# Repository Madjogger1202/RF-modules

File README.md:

# RF-modules

**Серия экспериментальных ВЧ-плат: широкополосные усилители и пассивные фильтры Чебышёва.**

Небольшая коллекция тестовых радиочастотных плат, собранная в процессе погружения в тему ВЧ-усилителей и согласования сигналов. Идея — спроектировать набор готовых строительных блоков (усилитель, транзисторный каскад, фильтры), чтобы в нужный момент сразу взять проверенный модуль с полки. Каждая плата оформлена как отдельный проект внутри репозитория.

## Состав репозитория

| Папка | Тип | Краткое описание |
|---|---|---|
| `BGA2869 amplifier` | Усилитель | MMIC-усилитель BGA2869, DC–2.2 ГГц, ~30 dB |
| `MMBF5485 amplifier` | Усилитель | Каскад на N-канальном ВЧ JFET MMBF5485 + обвязка |
| `Chebyshev_4_filter` | Фильтр | LC-фильтр Чебышёва 4-го порядка |
| `Chebyshev_10_filter` | Фильтр | LC-фильтр Чебышёва 10-го порядка |

---

## BGA2869 amplifier

Широкополосный усилитель на MMIC **BGA2869** (NXP) — недорогой и удобный «кирпичик» усиления с внутренним согласованием на 50 Ω, не требующий внешних согласующих цепей и выходного дросселя.

**Характеристики**

| Параметр | Значение |
|---|---|
| Активный элемент | BGA2869 (NXP MMIC, SOT363) |
| Полоса | DC … 2.2 ГГц |
| Усиление | ~31.7 dB @ 950 МГц |
| Коэффициент шума | 3.1 dB @ 950 МГц |
| Выходная мощность (P1dB) | ~10 dBm @ 950 МГц |
| Согласование | внутреннее, 50 Ω (вход/выход) |
| Питание | 5 В (~24 мА) |
| Вход питания | USB и DC-Jack |

Применение: универсальный широкополосный блок усиления, IF-усилитель, второй каскад после LNA. Сам чип стоит около 100 руб — плата получается очень бюджетной.

---

## MMBF5485 amplifier

Каскад на N-канальном ВЧ JFET **MMBF5485** (семейство 2N5484/5485/5486) с цепями смещения и согласования. Экспериментальная плата — основная цель проверить транзистор в роли ВЧ-усилителя. Если по усилению результат не устроит, обвязка спроектирована так, что плату можно переиспользовать как фильтр/согласующий модуль.

**Характеристики**

| Параметр | Значение |
|---|---|
| Активный элемент | MMBF5485 (N-канальный JFET, SOT-23) |
| Назначение | ВЧ-усилитель VHF/UHF диапазона |
| VGS(off) | −0.5 … −4 В |
| Крутизна (gfs) | от ~3.5 мС |
| Согласование | дискретная обвязка вход/выход |
| Резервное использование | фильтр / согласующий модуль |

---

## Фильтры Чебышёва (4 и 10 порядка)

Пассивные LC-фильтры с характеристикой Чебышёва: версии **4-го** (`Chebyshev_4_filter`) и **10-го** (`Chebyshev_10_filter`) порядков. Сделаны как готовые фильтрующие блоки на 50 Ω, чтобы держать под рукой для отладки и согласования трактов.

| Параметр | Chebyshev_4_filter | Chebyshev_10_filter |
|---|---|---|
| Тип | LC-фильтр Чебышёва | LC-фильтр Чебышёва |
| Порядок | 4 | 10 |
| Импеданс | 50 Ω | 50 Ω |
| Крутизна склона | пологая | крутая (больше секций) |

> 💡 Удобный онлайн-калькулятор LC-фильтров с подбором реальных номиналов компонентов:
> https://markimicrowave.com/technical-resources/tools/lc-filter-design-tool/

---

## Среда разработки

- **Схема и плата:** KiCad
- **Подбор фильтров:** Marki Microwave LC Filter Design Tool
- **Документация на компоненты:** datasheet BGA2869 (NXP), MMBF5485 (Fairchild/onsemi)

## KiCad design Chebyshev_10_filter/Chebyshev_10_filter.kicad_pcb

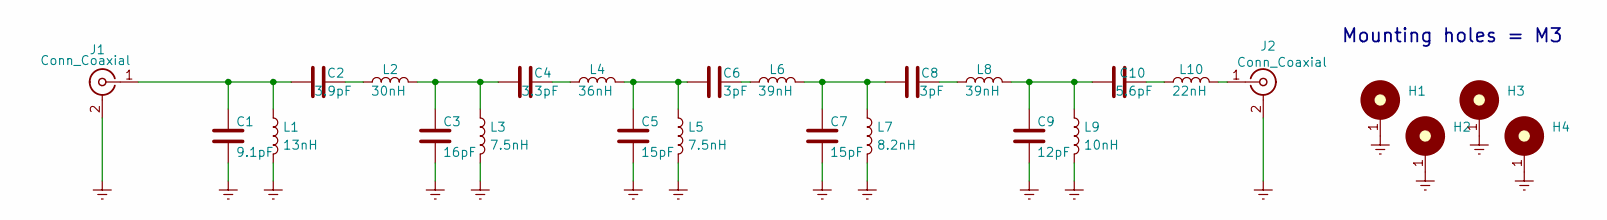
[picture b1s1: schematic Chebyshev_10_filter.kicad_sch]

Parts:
C1: 9.1pF; C_0402_1005Metric
C2: 3.9pF; C_0402_1005Metric
C3: 16pF; C_0402_1005Metric
C4: 3.3pF; C_0402_1005Metric
C5, C7: 15pF; C_0402_1005Metric
C6, C8: 3pF; C_0402_1005Metric
C9: 12pF; C_0402_1005Metric
C10: 5.6pF; C_0402_1005Metric
H1, H2, H3: MountingHole_M3_3.2mm_Pad; MountingHole_3.2mm_M3_DIN965_Pad_TopBottom
H4: MountingHole:MountingHole_3.2mm_M3_DIN965_Pad_Top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; MountingHole_3.2mm_M3_DIN965_Pad_TopBottom
J1, J2: Conn_Coaxial; SMA_Samtec_SMA-J-P-H-ST-EM1_EdgeMount
L1: 13nH; L_0402_1005Metric
L2: 30nH; L_0402_1005Metric
L3, L5: 7.5nH; L_0402_1005Metric
L4: 36nH; L_0402_1005Metric
L6, L8: 39nH; L_0402_1005Metric
L7: 8.2nH; L_0402_1005Metric
L9: 10nH; L_0402_1005Metric
L10: 22nH; L_0402_1005Metric

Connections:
Earth: C1.2, C3.2, C5.2, C7.2, C9.2, H1.1, H2.1, H3.1, H4.1, J1.2 (Ext), J2.2 (Ext), L1.2, L3.2, L5.2, L7.2, L9.2
unnamed: C2.2, L2.1
unnamed: C3.1, C4.1, L2.2, L3.1
unnamed: C4.2, L4.1
unnamed: C5.1, C6.1, L4.2, L5.1
unnamed: C6.2, L6.1
unnamed: C7.1, C8.1, L6.2, L7.1
unnamed: C8.2, L8.1
unnamed: C9.1, C10.1, L8.2, L9.1
unnamed: C10.2, L10.1
unnamed: C1.1, C2.1, J1.1 (In), L1.1
unnamed: J2.1 (In), L10.2

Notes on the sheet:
Mounting holes = M3

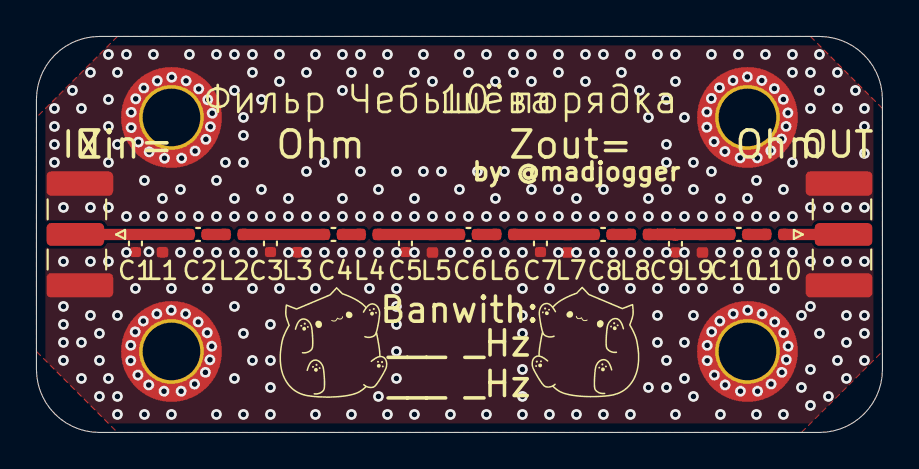
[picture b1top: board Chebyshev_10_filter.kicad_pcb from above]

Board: 2 copper layers, 47.0 x 22.0 mm, 26 parts (0 on the bottom side), 12 nets.

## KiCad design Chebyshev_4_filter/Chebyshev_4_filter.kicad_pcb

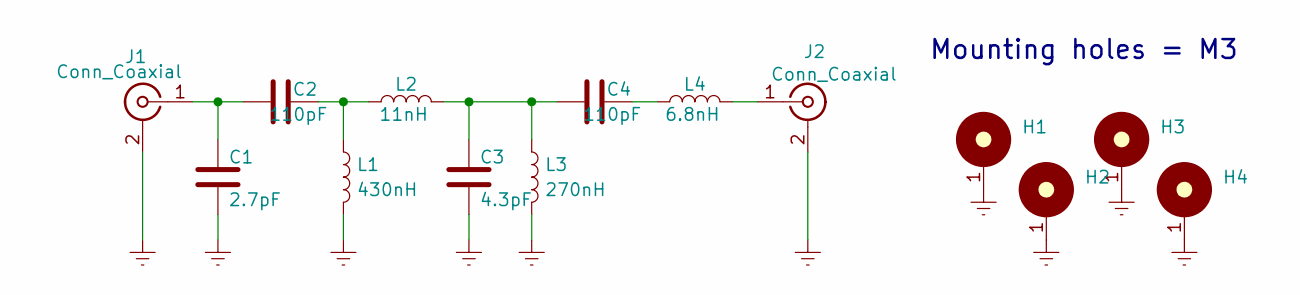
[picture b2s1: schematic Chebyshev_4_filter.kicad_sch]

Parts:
C1: 2.7pF; C_0402_1005Metric
C2, C4: 110pF; C_0402_1005Metric
C3: 4.3pF; C_0402_1005Metric
H1, H2, H3: MountingHole_M3_3.2mm_Pad; MountingHole_3.2mm_M3_DIN965_Pad_TopBottom
H4: MountingHole:MountingHole_3.2mm_M3_DIN965_Pad_Top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; MountingHole_3.2mm_M3_DIN965_Pad_TopBottom
J1, J2: Conn_Coaxial; SMA_Samtec_SMA-J-P-H-ST-EM1_EdgeMount
L1: 430nH; L_0402_1005Metric
L2: 11nH; L_0402_1005Metric
L3: 270nH; L_0402_1005Metric
L4: 6.8nH; L_0402_1005Metric

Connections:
Earth: C1.2, C3.2, H1.1, H2.1, H3.1, H4.1, J1.2 (Ext), J2.2 (Ext), L1.2, L3.2
unnamed: C2.2, L1.1, L2.1
unnamed: C3.1, C4.1, L2.2, L3.1
unnamed: C4.2, L4.1
unnamed: C1.1, C2.1, J1.1 (In)
unnamed: J2.1 (In), L4.2

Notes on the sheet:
Mounting holes = M3

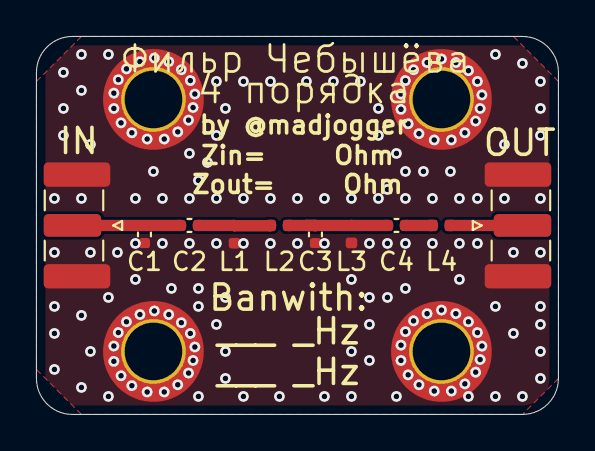
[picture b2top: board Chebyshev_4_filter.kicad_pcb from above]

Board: 2 copper layers, 29.0 x 21.0 mm, 14 parts (0 on the bottom side), 6 nets.

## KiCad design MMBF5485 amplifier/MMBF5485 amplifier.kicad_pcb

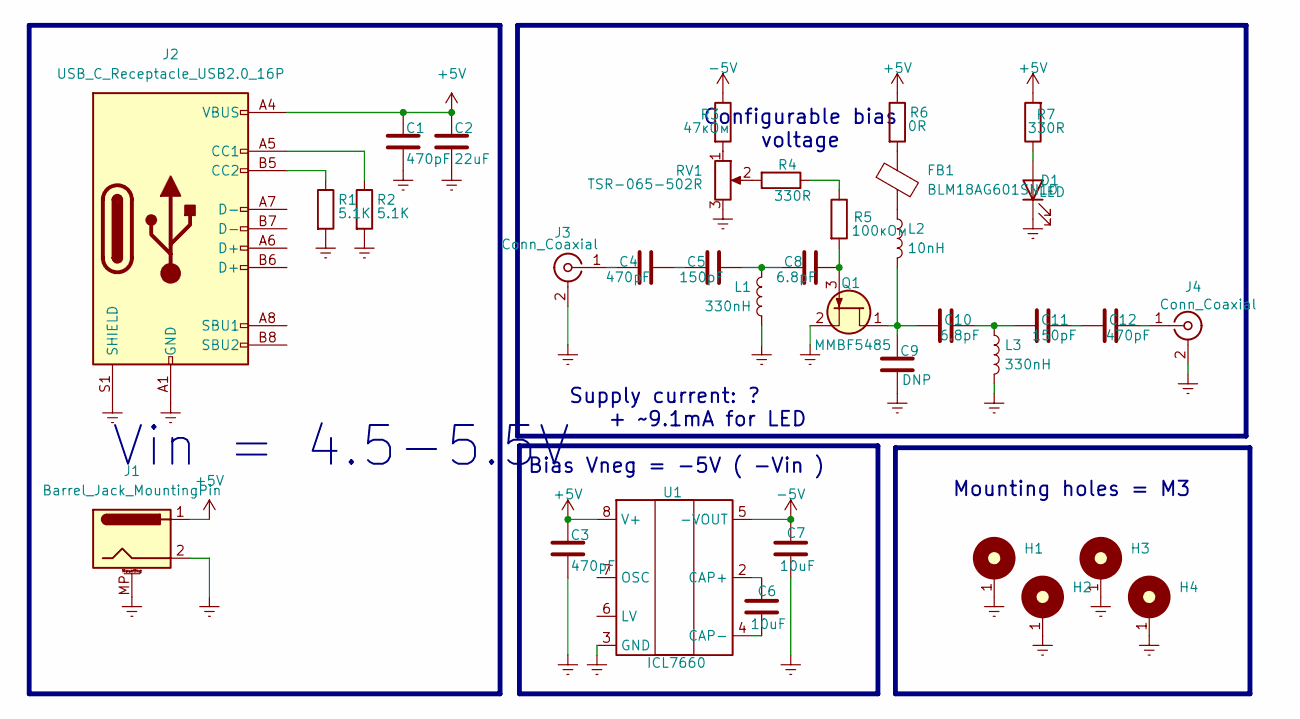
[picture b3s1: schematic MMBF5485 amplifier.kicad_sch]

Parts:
C1, C3, C4, C12: 470pF; C_0603_1608Metric
C2: 22uF; C_0603_1608Metric
C5, C11: 150pF; C_0603_1608Metric
C6, C7: 10uF; C_0603_1608Metric
C8, C10: 6.8pF; C_0603_1608Metric
C9: DNP; C_0603_1608Metric
D1: LED; LED_0603_1608Metric
FB1: BLM18AG601SN1D; L_0603_1608Metric
H1, H2, H3: MountingHole_M3_3.2mm_Pad; MountingHole_3.2mm_M3_DIN965_Pad_TopBottom
H4: MountingHole:MountingHole_3.2mm_M3_DIN965_Pad_Top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; MountingHole_3.2mm_M3_DIN965_Pad_TopBottom
J1: Barrel_Jack_MountingPin; BarrelJack_GCT_DCJ200-10-A_Horizontal
J2: USB_C_Receptacle_USB2.0_16P; USB_C_Receptacle_G-Switch_GT-USB-7010ASV
J3, J4: Conn_Coaxial; SMA_Samtec_SMA-J-P-H-ST-EM1_EdgeMount
L1, L3: 330nH; L_0805_2012Metric
L2: 10nH; L_0603_1608Metric
Q1: MMBF5485; SOT-23
R1, R2: 5.1K; R_0603_1608Metric
R3: 47кОм; R_0603_1608Metric
R4, R7: 330R; R_0603_1608Metric
R5: 100кОм; R_0603_1608Metric
R6: 0R; R_0603_1608Metric
RV1: TSR-065-502R; Potentiometer_RM065
U1: ICL7660; SOIC-8_3.9x4.9mm_P1.27mm

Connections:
+5V: C1.1, C2.1, C3.1, J1.1, J2.A4 (VBUS), J2.A9 (VBUS), J2.B4 (VBUS), J2.B9 (VBUS), R6.1, R7.2, U1.8 (V+)
-5V: C7.2, R3.1, U1.5 (-VOUT)
Earth: C1.2, C2.2, C3.2, C7.1, C9.2, D1.1 (K), H1.1, H2.1, H3.1, H4.1, J1.2, J1.MP (MountPin), J2.A1 (GND), J2.A12 (GND), J2.B1 (GND), J2.B12 (GND), J2.S1 (SHIELD), J3.2 (Ext), J4.2 (Ext), L1.2, L3.2, Q1.2 (S), R1.2, R2.2, RV1.3, U1.3 (GND)
unnamed: C4.1, C5.2
unnamed: C5.1, C8.2, L1.1
unnamed: C10.2, C11.1, L3.1
unnamed: C11.2, C12.1
unnamed: D1.2 (A), R7.1
unnamed: FB1.1, R6.2
unnamed: FB1.2, L2.1
unnamed: J2.A5 (CC1), R2.1
unnamed: J2.B5 (CC2), R1.1
unnamed: C4.2, J3.1 (In)
unnamed: C12.2, J4.1 (In)
unnamed: C9.1, C10.1, L2.2, Q1.1 (D)
unnamed: C8.1, Q1.3 (G), R5.2
unnamed: R3.2, RV1.1
unnamed: R4.1, R5.1
unnamed: R4.2, RV1.2
unnamed: C6.2, U1.2 (CAP+)
unnamed: C6.1, U1.4 (CAP-)

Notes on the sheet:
Configurable bias voltage
Bias Vneg = -5V ( -Vin )
Mounting holes = M3
Supply current: ?
+ ~9.1mA for LED
Vin = 4.5-5.5V

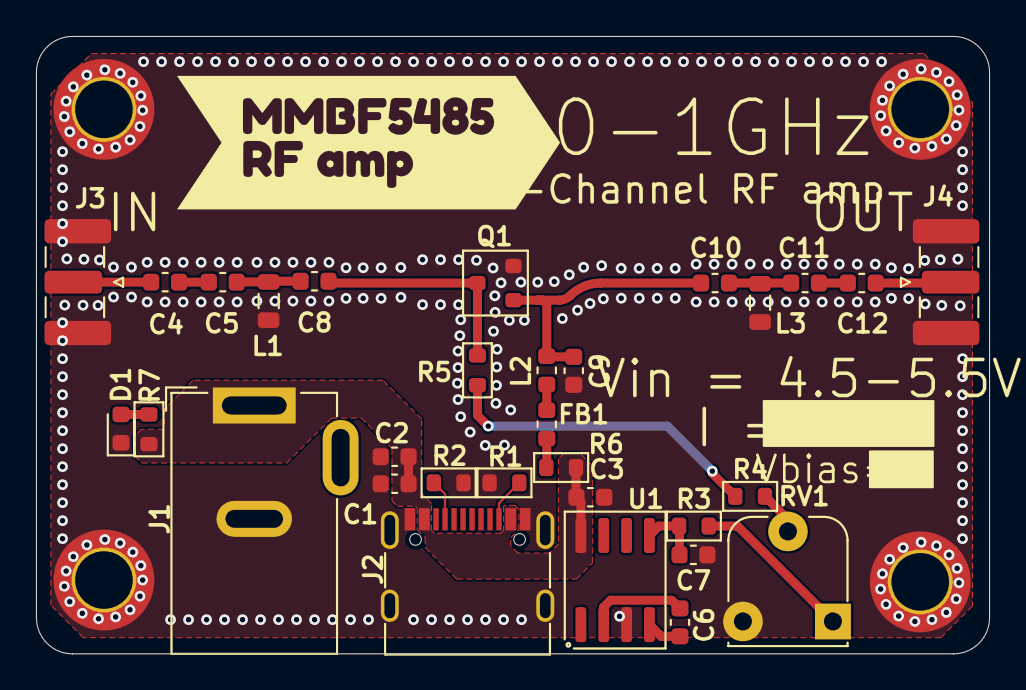
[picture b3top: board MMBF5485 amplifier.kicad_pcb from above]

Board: 2 copper layers, 53.0 x 34.3 mm, 36 parts (0 on the bottom side), 21 nets.

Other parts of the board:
kibuzzard-68160865: G***; kibuzzard-68160865

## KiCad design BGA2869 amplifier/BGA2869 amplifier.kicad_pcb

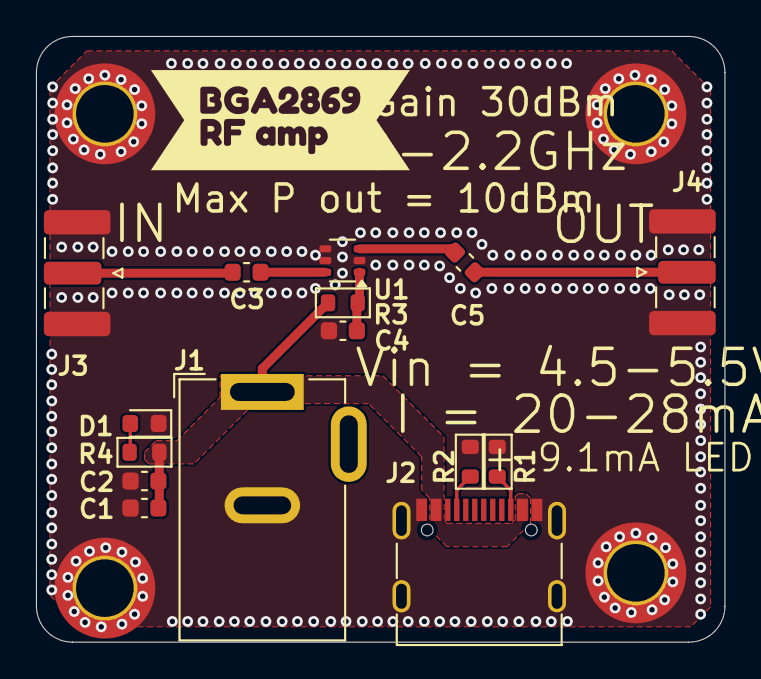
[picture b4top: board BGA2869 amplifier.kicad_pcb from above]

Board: 2 copper layers, 38.2 x 33.6 mm, 20 parts (0 on the bottom side), 10 nets.

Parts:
C1, C3, C4, C5: 470pF; C_0603_1608Metric
C2: 22uF; C_0603_1608Metric
D1: LED; LED_0603_1608Metric
H1, H2, H3: MountingHole_M3_3.2mm_Pad; MountingHole_3.2mm_M3_DIN965_Pad_TopBottom
H4: MountingHole:MountingHole_3.2mm_M3_DIN965_Pad_Top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; MountingHole_3.2mm_M3_DIN965_Pad_TopBottom
J1: Barrel_Jack_MountingPin; BarrelJack_GCT_DCJ200-10-A_Horizontal
J2: USB_C_Receptacle_USB2.0_16P; USB_C_Receptacle_G-Switch_GT-USB-7010ASV
J3, J4: Conn_Coaxial; SMA_Samtec_SMA-J-P-H-ST-EM1_EdgeMount
R1, R2: 5.1K; R_0603_1608Metric
R3: 0R; R_0603_1608Metric
R4: 330R; R_0603_1608Metric
U1: BGA2869; SOT-363_SC-70-6
kibuzzard-68154E88: G***; kibuzzard-68154E88

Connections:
+5V: C1.1, C2.1, J1.1, J2.A4 (VBUS), J2.A9 (VBUS), J2.B4 (VBUS), J2.B9 (VBUS), R3.1, R4.2
Earth: C1.2, C2.2, C4.2, D1.1 (K), H1.1, H2.1, H3.1, H4.1, J1.2, J2.A1 (GND), J2.A12 (GND), J2.B1 (GND), J2.B12 (GND), J2.S1 (SHIELD), J3.2 (Ext), J4.2 (Ext), R1.2, R2.2, U1.2 (G), U1.4 (G), U1.5 (G)
unnamed: C3.1, U1.6
unnamed: C5.1, U1.3
unnamed: D1.2 (A), R4.1
unnamed: J2.A5 (CC1), R2.1
unnamed: J2.B5 (CC2), R1.1
unnamed: C3.2, J3.1 (In)
unnamed: C5.2, J4.1 (In)
unnamed: C4.1, R3.2, U1.1 (Vcc)

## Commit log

2025-05-02 rev0 BGA2869 amp
2025-05-03 MMBF5485 amp rev0
2025-05-03 забыл плату)
2025-05-26 Добавил проекты фильтров Чебышёва
